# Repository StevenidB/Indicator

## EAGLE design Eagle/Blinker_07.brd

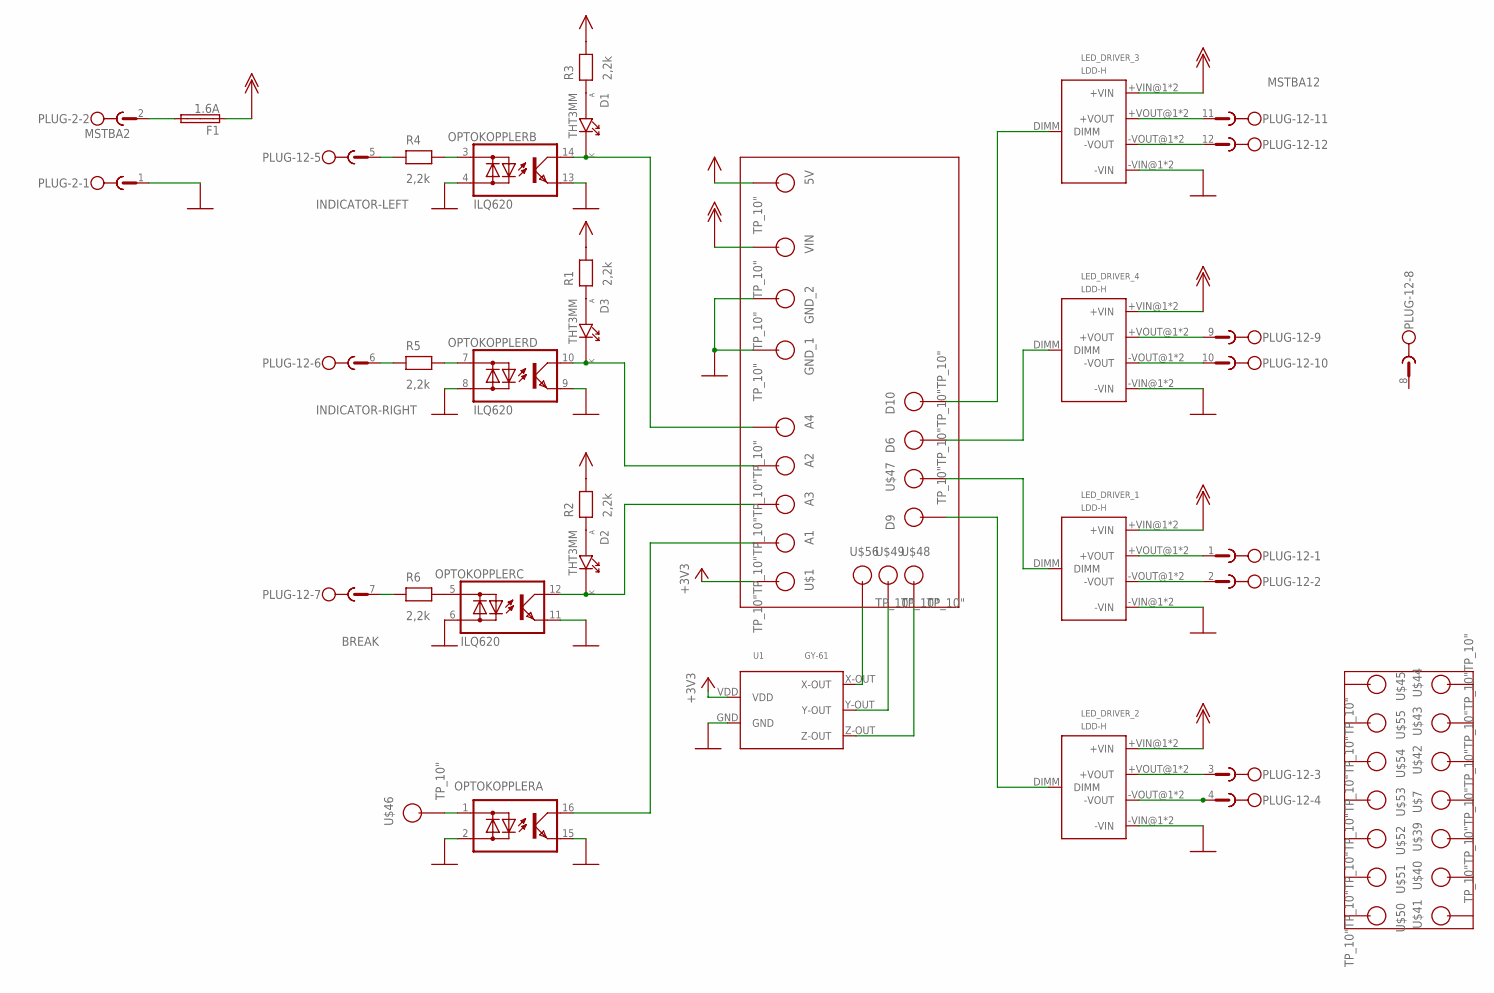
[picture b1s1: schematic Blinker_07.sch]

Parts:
5V: TP_10"; TP_10
A1, A2, A3, A4: TP_10"; TP_10
D1, D2, D3: THT3MM
D6, D9, D10: TP_10"; TP_10
F1: 1.6A; SHK20Q
GND_1, GND_2: TP_10"; TP_10
LED_DRIVER_1, LED_DRIVER_2, LED_DRIVER_3, LED_DRIVER_4: LDD-H
OPTOKOPPLER: ILQ620; DIL16
PLUG-2: MSTBA2
PLUG-12: MSTBA12
R1, R2, R3, R4, R5, R6: 2,2k; R-10
U1: GY-61
U$1, U$7, U$39, U$40, U$41, U$42, U$43, U$44, U$45, U$46, U$47, U$48, U$49, U$50, U$51, U$52, U$53, U$54, U$55, U$56: TP_10"; TP_10
VIN: TP_10"; TP_10

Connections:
+3V3: U1.VDD, U$1.P$1
+5V: 5V.P$1, R1.2, R2.2, R3.2
+12V: F1.1A, LED_DRIVER_1.+VIN@1 (+VIN), LED_DRIVER_1.+VIN@2 (+VIN), LED_DRIVER_2.+VIN@1 (+VIN), LED_DRIVER_2.+VIN@2 (+VIN), LED_DRIVER_3.+VIN@1 (+VIN), LED_DRIVER_3.+VIN@2 (+VIN), LED_DRIVER_4.+VIN@1 (+VIN), LED_DRIVER_4.+VIN@2 (+VIN), VIN.P$1
BLAULICHT: LED_DRIVER_2.-VOUT@1 (-VOUT), LED_DRIVER_2.-VOUT@2 (-VOUT), PLUG-12.4
BLUE-LED: D6.P$1, LED_DRIVER_4.DIMM
BREAK: PLUG-12.7, R6.1
BREAK-LED: D10.P$1, LED_DRIVER_3.DIMM
GND: GND_1.P$1, GND_2.P$1, LED_DRIVER_1.-VIN@1 (-VIN), LED_DRIVER_1.-VIN@2 (-VIN), LED_DRIVER_2.-VIN@1 (-VIN), LED_DRIVER_2.-VIN@2 (-VIN), LED_DRIVER_3.-VIN@1 (-VIN), LED_DRIVER_3.-VIN@2 (-VIN), LED_DRIVER_4.-VIN@1 (-VIN), LED_DRIVER_4.-VIN@2 (-VIN), OPTOKOPPLER.2 (AC2), OPTOKOPPLER.4 (AC2), OPTOKOPPLER.6 (AC2), OPTOKOPPLER.8 (AC2), OPTOKOPPLER.9 (E), OPTOKOPPLER.11 (E), OPTOKOPPLER.13 (E), OPTOKOPPLER.15 (E), PLUG-2.1, U1.GND
INDICATOR-LEFT: PLUG-12.5, R4.1
INDICATOR-RIGHT: PLUG-12.6, R5.1
LED_2: D1.A (P1A), R3.1
LEFT-LED: LED_DRIVER_1.DIMM, U$47.P$1
unnamed: F1.2A, PLUG-2.2
unnamed: D3.A (P1A), R1.1
unnamed: A3.P$1, D2.K (P2K), OPTOKOPPLER.12 (C)
unnamed: OPTOKOPPLER.1 (AC1), U$46.P$1
unnamed: A1.P$1, OPTOKOPPLER.16 (C)
unnamed: OPTOKOPPLER.7 (AC1), R5.2
unnamed: U1.X-OUT, U$56.P$1
unnamed: U1.Y-OUT, U$49.P$1
unnamed: LED_DRIVER_1.+VOUT@1 (+VOUT), LED_DRIVER_1.+VOUT@2 (+VOUT), PLUG-12.1
unnamed: LED_DRIVER_1.-VOUT@1 (-VOUT), LED_DRIVER_1.-VOUT@2 (-VOUT), PLUG-12.2
unnamed: LED_DRIVER_2.+VOUT@1 (+VOUT), LED_DRIVER_2.+VOUT@2 (+VOUT), PLUG-12.3
unnamed: LED_DRIVER_3.-VOUT@1 (-VOUT), LED_DRIVER_3.-VOUT@2 (-VOUT), PLUG-12.12
unnamed: LED_DRIVER_3.+VOUT@1 (+VOUT), LED_DRIVER_3.+VOUT@2 (+VOUT), PLUG-12.11
unnamed: LED_DRIVER_4.-VOUT@1 (-VOUT), LED_DRIVER_4.-VOUT@2 (-VOUT), PLUG-12.10
unnamed: D2.A (P1A), R2.1
unnamed: LED_DRIVER_4.+VOUT@1 (+VOUT), LED_DRIVER_4.+VOUT@2 (+VOUT), PLUG-12.9
unnamed: OPTOKOPPLER.5 (AC1), R6.2
unnamed: U1.Z-OUT, U$48.P$1
unnamed: OPTOKOPPLER.3 (AC1), R4.2
RIGHT-LED: D9.P$1, LED_DRIVER_2.DIMM
SCH_LI_3: A2.P$1, D3.K (P2K), OPTOKOPPLER.10 (C)
SCH_RE_3: A4.P$1, D1.K (P2K), OPTOKOPPLER.14 (C)

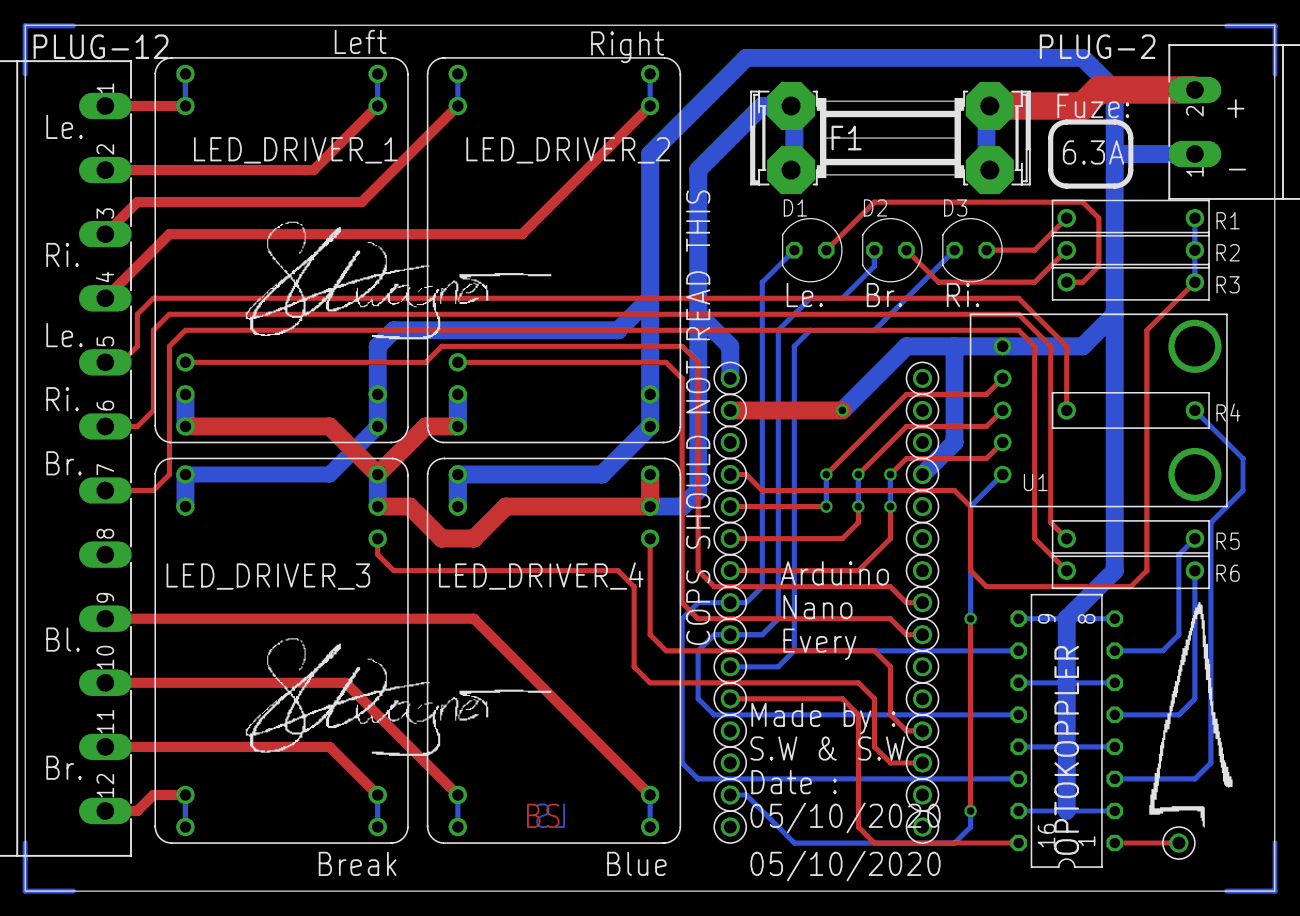
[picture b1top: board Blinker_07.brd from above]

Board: 2 copper layers, 99.0 x 68.6 mm, 49 parts (0 on the bottom side), 34 nets.

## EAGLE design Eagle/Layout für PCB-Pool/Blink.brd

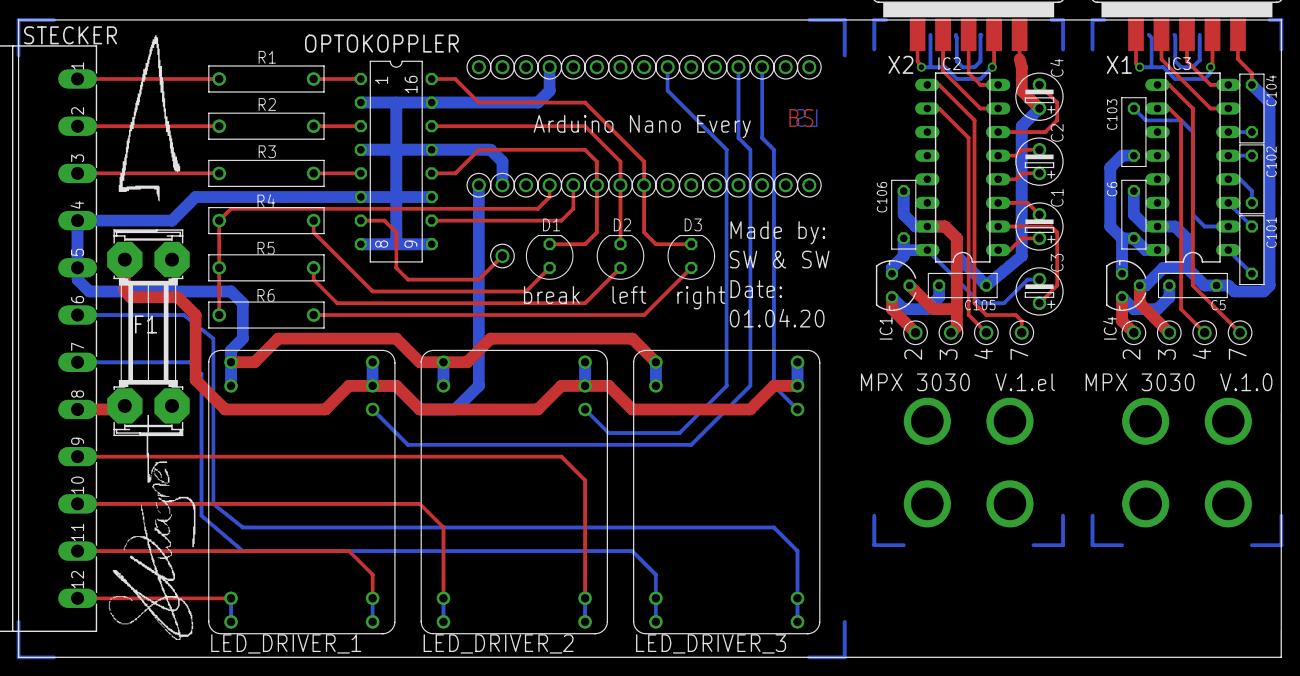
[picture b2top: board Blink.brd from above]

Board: 2 copper layers, 135.9 x 68.6 mm, 80 parts (0 on the bottom side), 57 nets.

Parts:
1, 2, 3, 4, 5, 6, 7, 8: TP_10
5V: TP_10"; TP_10
A4, A5, A6, A7: TP_10"; TP_10
C1, C2: 1µ; ES-2,5L
C3, C4: 10µ; ES-2,5L
C5, C6, C102, C103, C104, C105, C106: C050-025X075
C101: 100n; C050-025X075
D1, D2, D3: THT3MM
D6, D9, D10: TP_10"; TP_10
F1: 1.6A; SHK20Q
GND_1, GND_2: TP_10"; TP_10
IC1, IC4: 78L05; 78LXX
IC2, IC3: MAX3232CPE; DIL16
LED_DRIVER_1, LED_DRIVER_2, LED_DRIVER_3: LDD-H
OPTOKOPPLER: ILQ620; DIL16
R1, R2, R3, R4, R5, R6: 2,2k; R-10
STECKER: MSTBA12
TESTPUNKT: TP_10"; TP_10
U$1, U$2, U$3, U$4, U$5, U$6, U$8, U$9: TP_35
U$7, U$39, U$40, U$41, U$42, U$43, U$44, U$45, U$46, U$47, U$48, U$49, U$50, U$51, U$52, U$53, U$54, U$55, U$56: TP_10"; TP_10
VIN: TP_10"; TP_10
X1, X2: F09D

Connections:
+5V: 5V.P$1, R4.2, R5.2, R6.2
+5V1: C3.2, C106.2, IC1.OUT, IC2.16
+5V2: C6.2, C103.2, IC3.16, IC4.OUT
+12V: F1.2A, LED_DRIVER_1.+VIN@1, LED_DRIVER_1.+VIN@2, LED_DRIVER_2.+VIN@1, LED_DRIVER_2.+VIN@2, LED_DRIVER_3.+VIN@1, LED_DRIVER_3.+VIN@2, VIN.P$1
+VOUT_1: LED_DRIVER_1.+VOUT@1, LED_DRIVER_1.+VOUT@2, STECKER.11
+VOUT_2: LED_DRIVER_2.+VOUT@1, LED_DRIVER_2.+VOUT@2, STECKER.9
+VOUT_3: LED_DRIVER_3.+VOUT@1, LED_DRIVER_3.+VOUT@2, STECKER.6
-VOUT_1: LED_DRIVER_1.-VOUT@1, LED_DRIVER_1.-VOUT@2, STECKER.12
-VOUT_2: LED_DRIVER_2.-VOUT@1, LED_DRIVER_2.-VOUT@2, STECKER.10
-VOUT_3: LED_DRIVER_3.-VOUT@1, LED_DRIVER_3.-VOUT@2, STECKER.7
A_CABLE_PIN_1: 6.P$1, IC3.9
A_CABLE_PIN_7: 7.P$1, IC2.9
A_DSUB: IC2.8, X2.3
A_DSUB1: IC3.8, X1.3
B_CABLE_PIN_1: 8.P$1, IC3.10
B_CABLE_PIN_4: 4.P$1, IC2.10
B_DSUB: IC2.7, X2.2
B_DSUB1: IC3.7, X1.2
CABLE_PIN_1: 1.P$1, C5.2, IC4.IN
CABLE_PIN_2: 2.P$1, C105.2, IC1.IN
DIMMER_1: D9.P$1, LED_DRIVER_1.DIMM
DIMMER_2: D6.P$1, LED_DRIVER_2.DIMM
DIMMER_3: D10.P$1, LED_DRIVER_3.DIMM
GND: GND_1.P$1, GND_2.P$1, LED_DRIVER_1.-VIN@1, LED_DRIVER_1.-VIN@2, LED_DRIVER_2.-VIN@1, LED_DRIVER_2.-VIN@2, LED_DRIVER_3.-VIN@1, LED_DRIVER_3.-VIN@2, OPTOKOPPLER.2, OPTOKOPPLER.4, OPTOKOPPLER.6, OPTOKOPPLER.8, OPTOKOPPLER.9, OPTOKOPPLER.11, OPTOKOPPLER.13, OPTOKOPPLER.15, STECKER.4, STECKER.5
GND1: 3.P$1, C4.1, C105.1, C106.1, IC1.GND, IC2.15, X2.5
GND2: 5.P$1, C5.1, C6.1, C104.2, IC3.15, IC4.GND, X1.5
LED_1: D1.A, R4.1
LED_2: D2.A, R5.1
LED_3: D3.A, R6.1
unnamed: F1.1A, STECKER.8
unnamed: X2.7, X2.8
unnamed: X2.1, X2.4, X2.6
unnamed: C101.2, IC3.1
unnamed: C101.1, IC3.3
unnamed: C102.2, IC3.4
unnamed: C102.1, IC3.5
unnamed: C103.1, IC3.2
unnamed: C104.1, IC3.6
unnamed: X1.7, X1.8
unnamed: X1.1, X1.4, X1.6
unnamed: C1.1, IC2.1
unnamed: C1.2, IC2.3
unnamed: C2.1, IC2.4
unnamed: C2.2, IC2.5
unnamed: C3.1, IC2.2
unnamed: C4.2, IC2.6
RESERVE_1: OPTOKOPPLER.7, TESTPUNKT.P$1
RESERVE_2: A7.P$1, OPTOKOPPLER.10
SCHALTER_LI_1: R2.1, STECKER.2
SCHALTER_RE_1: R1.1, STECKER.1
SCHALTER_RUE_1: R3.1, STECKER.3
SCH_LI_2: OPTOKOPPLER.3, R2.2
SCH_LI_3: A5.P$1, D2.K, OPTOKOPPLER.14
SCH_RE_2: OPTOKOPPLER.1, R1.2
SCH_RE_3: A4.P$1, D3.K, OPTOKOPPLER.16
SCH_RUE_2: OPTOKOPPLER.5, R3.2
SCH_RUE_3: A6.P$1, D1.K, OPTOKOPPLER.12

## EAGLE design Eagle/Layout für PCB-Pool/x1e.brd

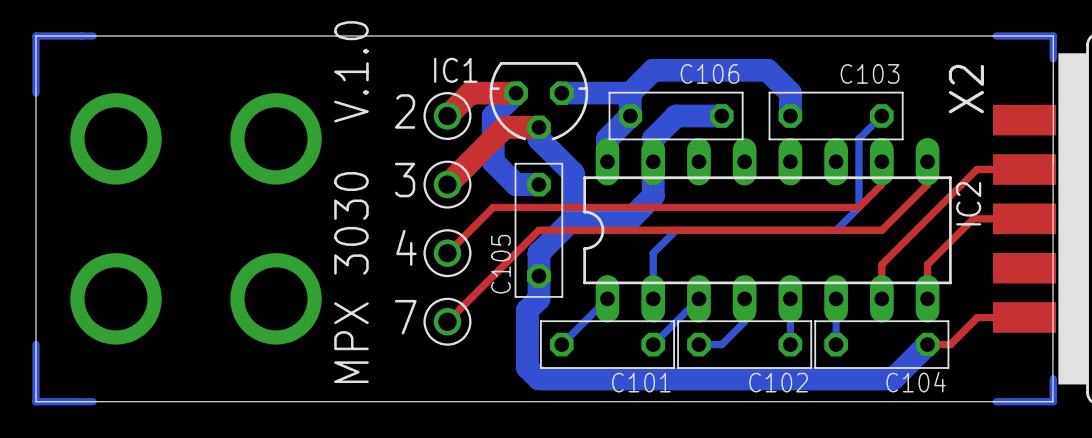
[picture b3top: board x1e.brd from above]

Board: 2 copper layers, 56.5 x 20.3 mm, 17 parts (0 on the bottom side), 13 nets.

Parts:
2, 3, 4, 7: TP_10
C101: 100n; C050-025X075
C102, C103, C104, C105, C106: C050-025X075
IC1: 78L05; 78LXX
IC2: MAX3232CPE; DIL16
U$1, U$2, U$3, U$4: TP_35
X2: F09D

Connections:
+5V: C103.2, C106.2, IC1.OUT, IC2.16
A_CABLE_PIN_7: 7.P$1, IC2.9
A_DSUB: IC2.8, X2.3
B_CABLE_PIN_4: 4.P$1, IC2.10
B_DSUB: IC2.7, X2.2
CABLE_PIN_2: 2.P$1, C105.2, IC1.IN
GND: 3.P$1, C104.2, C105.1, C106.1, IC1.GND, IC2.15, X2.5
unnamed: C101.2, IC2.1
unnamed: C101.1, IC2.3
unnamed: C102.2, IC2.4
unnamed: C102.1, IC2.5
unnamed: C103.1, IC2.2
unnamed: C104.1, IC2.6

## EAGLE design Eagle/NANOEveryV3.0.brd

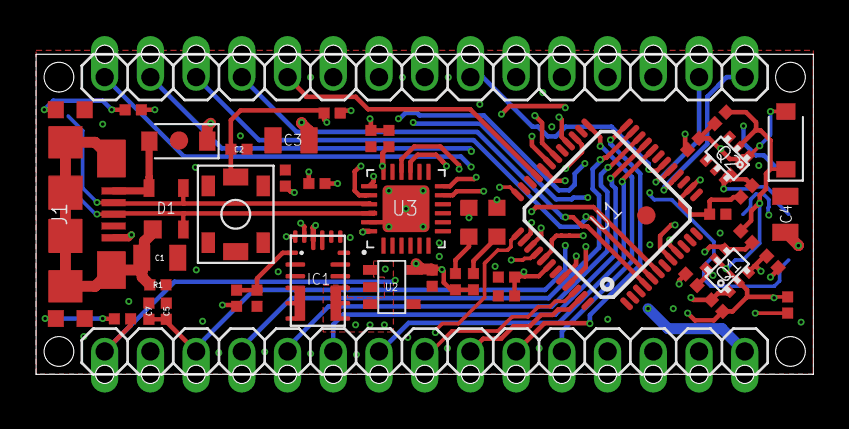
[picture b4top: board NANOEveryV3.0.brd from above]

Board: 4 copper layers, 43.2 x 17.8 mm, 54 parts (0 on the bottom side), 49 nets.

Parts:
C1: 4n7; 0805-R2013X50N
C2, C7, C8, C10, C11: 100n; 0402-1005X55N
C3, C4: 22u; 0805-R2013X50N
C5, C9: 4u7; 0402-1005X55N
C6: 1u; 0402-1005X55N
D1: PRTR5V; SOT190P230X110-4N
D2: PMEG6020; SODFL3517X110N
D3: DNP; SODFL3517X110N
D+: DNP; TP-1.00MM
D-: DNP; TP-1.00MM
DL1, DL3, DL4: YELLOW; LEDC1608X80N-AK
DL2: GREEN; LEDC1608X80N-AK
FD1, FD2: DNP; FD-1-1.5
FRAME1: DNP; FRAME
IC1: MPM3610
J1: -; ZX62-AB-5PA
J2: DNP; 2X03-TP
JP2, JP3: -; 1X15-CASTELL
PB1: PTS820; C&K_PTS820_NO_HOLES
Q1, Q2: BSS138PS; SOT363
R1: 1M; 0402-1005X55N
R2, R3, R12, R13: 330R; 0402-1005X55N
R4, R6, R10: 100k; 0402-1005X55N
R5, R11, R14, R15, R16, R17, R18, R19: 4k7; 0402-1005X55N
R7: 0R; 0402-1005X55N
R8: 19k1; 0402-1005X55N
R9: 39k; 0402-1005X55N
R20: DNP; 0402-1005X55N
U1: ATMEGA4809; TQFP48
U2: AP2112K-3.3; SOT25
U3: ATSAMD11D14A; HVQFN24

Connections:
+3V3: C6.1, C11.2, D3.C, J2.1, JP2.2, Q1.2, Q1.5, Q2.2, R2.2, R5.2, R11.1, R12.2, R13.2, R14.2, R16.2, R18.2, U2.5, U3.24
+5V: C3.1, C8.2, C9.2, C10.2, D2.C, IC1.7, IC1.8, IC1.9, IC1.20, JP2.12, R4.2, R6.2, R15.2, R17.2, R19.2, U1.14, U1.28, U1.42, U2.1, U2.3
A0: JP2.4, U1.23
A1: JP2.5, U1.22
A2: JP2.6, U1.21
A3: JP2.7, U1.20
A4/SDA: JP2.8, U1.36, U1.46
A5/SCL: JP2.9, U1.37, U1.47
A6: JP2.10, U1.24
A7: JP2.11, U1.25
AREF: C5.1, C7.1, JP2.3, U1.27
D2: JP3.5, U1.44
D3~: JP3.6, U1.39
D4: JP3.7, U1.18
D5~: JP3.8, U1.6
D6~: JP3.9, U1.38
D7: JP3.10, U1.45
D8: JP3.11, U1.33
D9~: JP3.12, U1.4
D10~: JP3.13, U1.5
D11_RESET: J2.6, R5.1, U3.18
D11_SWCLK: J2.3, R11.2, U3.19
D11_SWDIO: J2.2, U3.20
GND: C1.2, C2.2, C3.2, C4.2, C5.2, C6.2, C7.2, C8.1, C9.1, C10.1, C11.1, DL1.C, DL2.C, IC1.3, IC1.12, IC1.13, IC1.14, J1.5, J2.5, JP2.14, JP3.4, PB1.1, PB1.2, PB1.3, PB1.4, PB1.5, R1.1, R8.1, R9.1, U1.15, U1.29, U1.43, U2.2, U3.23, U3.EXP
MISO: JP3.15, U1.31
MOSI: JP3.14, U1.30
unnamed: C1.1, D1.1, J1.6, J1.7, J1.8, J1.9, J1.10, J1.11, R1.2
unnamed: DL2.A, R2.1
unnamed: DL1.A, R3.1
unnamed: IC1.1, R6.1, R8.2
unnamed: IC1.18, R9.2
unnamed: IC1.17, R10.1
unnamed: DL3.A, R12.1
unnamed: DL4.A, R13.1
RESETN: C2.1, JP2.13, JP3.3, PB1.6, R4.1, U1.40
RX0: Q1.6, R17.1, U1.9
RX1: JP3.2, U1.17
RX_D11: DL3.C, Q1.4, R14.1, U3.16
RX_UPDI: R7.2, U3.12
SCK: JP2.1, R3.2, U1.32
TX0: Q1.3, R15.1, U1.8
TX1: JP3.1, U1.16
TX_D11: DL4.C, Q1.1, R16.1, U3.15
TX_UPDI: D3.A, Q2.1, R7.1, R18.1, R20.1, U3.11
UPDI: J2.4, Q2.6, R19.1, R20.2, U1.41
USB_N: D1.3, D-.X, J1.2, U3.21
USB_P: D1.2, D+.X, J1.3, U3.22
VIN: C4.1, IC1.16, JP2.15, R10.2
VUSB: D1.4, D2.A, J1.1

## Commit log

2020-03-23 Test Commit
2020-03-24 Ordnen der Dateien/03/24/2020
2020-03-24 Einkaufsliste
2020-03-24 Arduino files
2020-03-27 Arbeiten SW & SW zum 24.03.2020
2020-03-28 Platinendesign
2020-03-28 Bermerkungen
2020-03-29 Arbeiten SW & SW zum 28.03.2020
2020-03-30 New text document -> Overview ; Eagle Ordner
2020-03-30 Sicherung & Logo
2020-03-31 Pfad gelöscht
2020-03-31 SWE: Board for PCB-Pool
2020-03-31 Cleanup
2020-03-31 SWE: Nutzen für PCB-Pool
2020-04-01 SWE: Bestellungen
2020-04-18 Arduino Programm
2020-04-20 Platine V2.0
2020-04-28 New Platine V2.1
2020-05-05 Net Width
2020-05-09 GY-61 introduction
2020-05-10 GY-61 Version 7.1
2020-05-11 7.2 - Finished
2020-05-12 7.2 Mutter freigelegt
2020-05-12 7.2 Fehlerbehebung
2020-05-12 7.2 große löcher
2020-11-12 Arduino Programm shortcut

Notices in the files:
Eagle/NANOEveryV3.0.brd:
Copyright (c) 2016-2017 Arduino LLC.  All right reserved. EAGLE Design Rules
parts and their libraries:
Arduino-utility: This work is licensed under a Creative Commons Attribution-ShareAlike 4.0 International License.
Arduino-connectors: Copyright (c) 2016-2017 Arduino LLC.  All right reserved.
